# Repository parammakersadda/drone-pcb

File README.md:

# SNI drone (Stm32 + Nrf24l01+ + Imu drone)

(under early stage development)

open source drone printed circuit board design with 4 coreless motors,  
using [stm32f103c8](https://www.st.com/en/microcontrollers-microprocessors/stm32f103c8.html) microcontroller chip for processing data and motor control,  
and [nrf24l01+](https://www.nordicsemi.com/Products/nRF24-series) 2.4Ghz radio transciever chip for wireless communication.

# LICENSE

Licensed under CERN Open Hardware Licence Version 2 - Weakly Reciprocal  
check "LICENSE" file for the license

# Images

There are 3d model files available in the 3dModels folder, in both stl and glb file formats.

Pcb manufacturing files (gerbers) are exported into the **exports** folder

(schematic and the copper routing)'s PDF files are available in the **PDFs** folder

[3d model (stl)](3dModels/drone-pcb.stl)  

front  

back  

[Schematics (click on this link to see the PDF)](PDFs/drone-pcb.pdf)

[Pcb routing (click on this link to see the PDF)](PDFs/drone-pcb-B_Cu.pdf)

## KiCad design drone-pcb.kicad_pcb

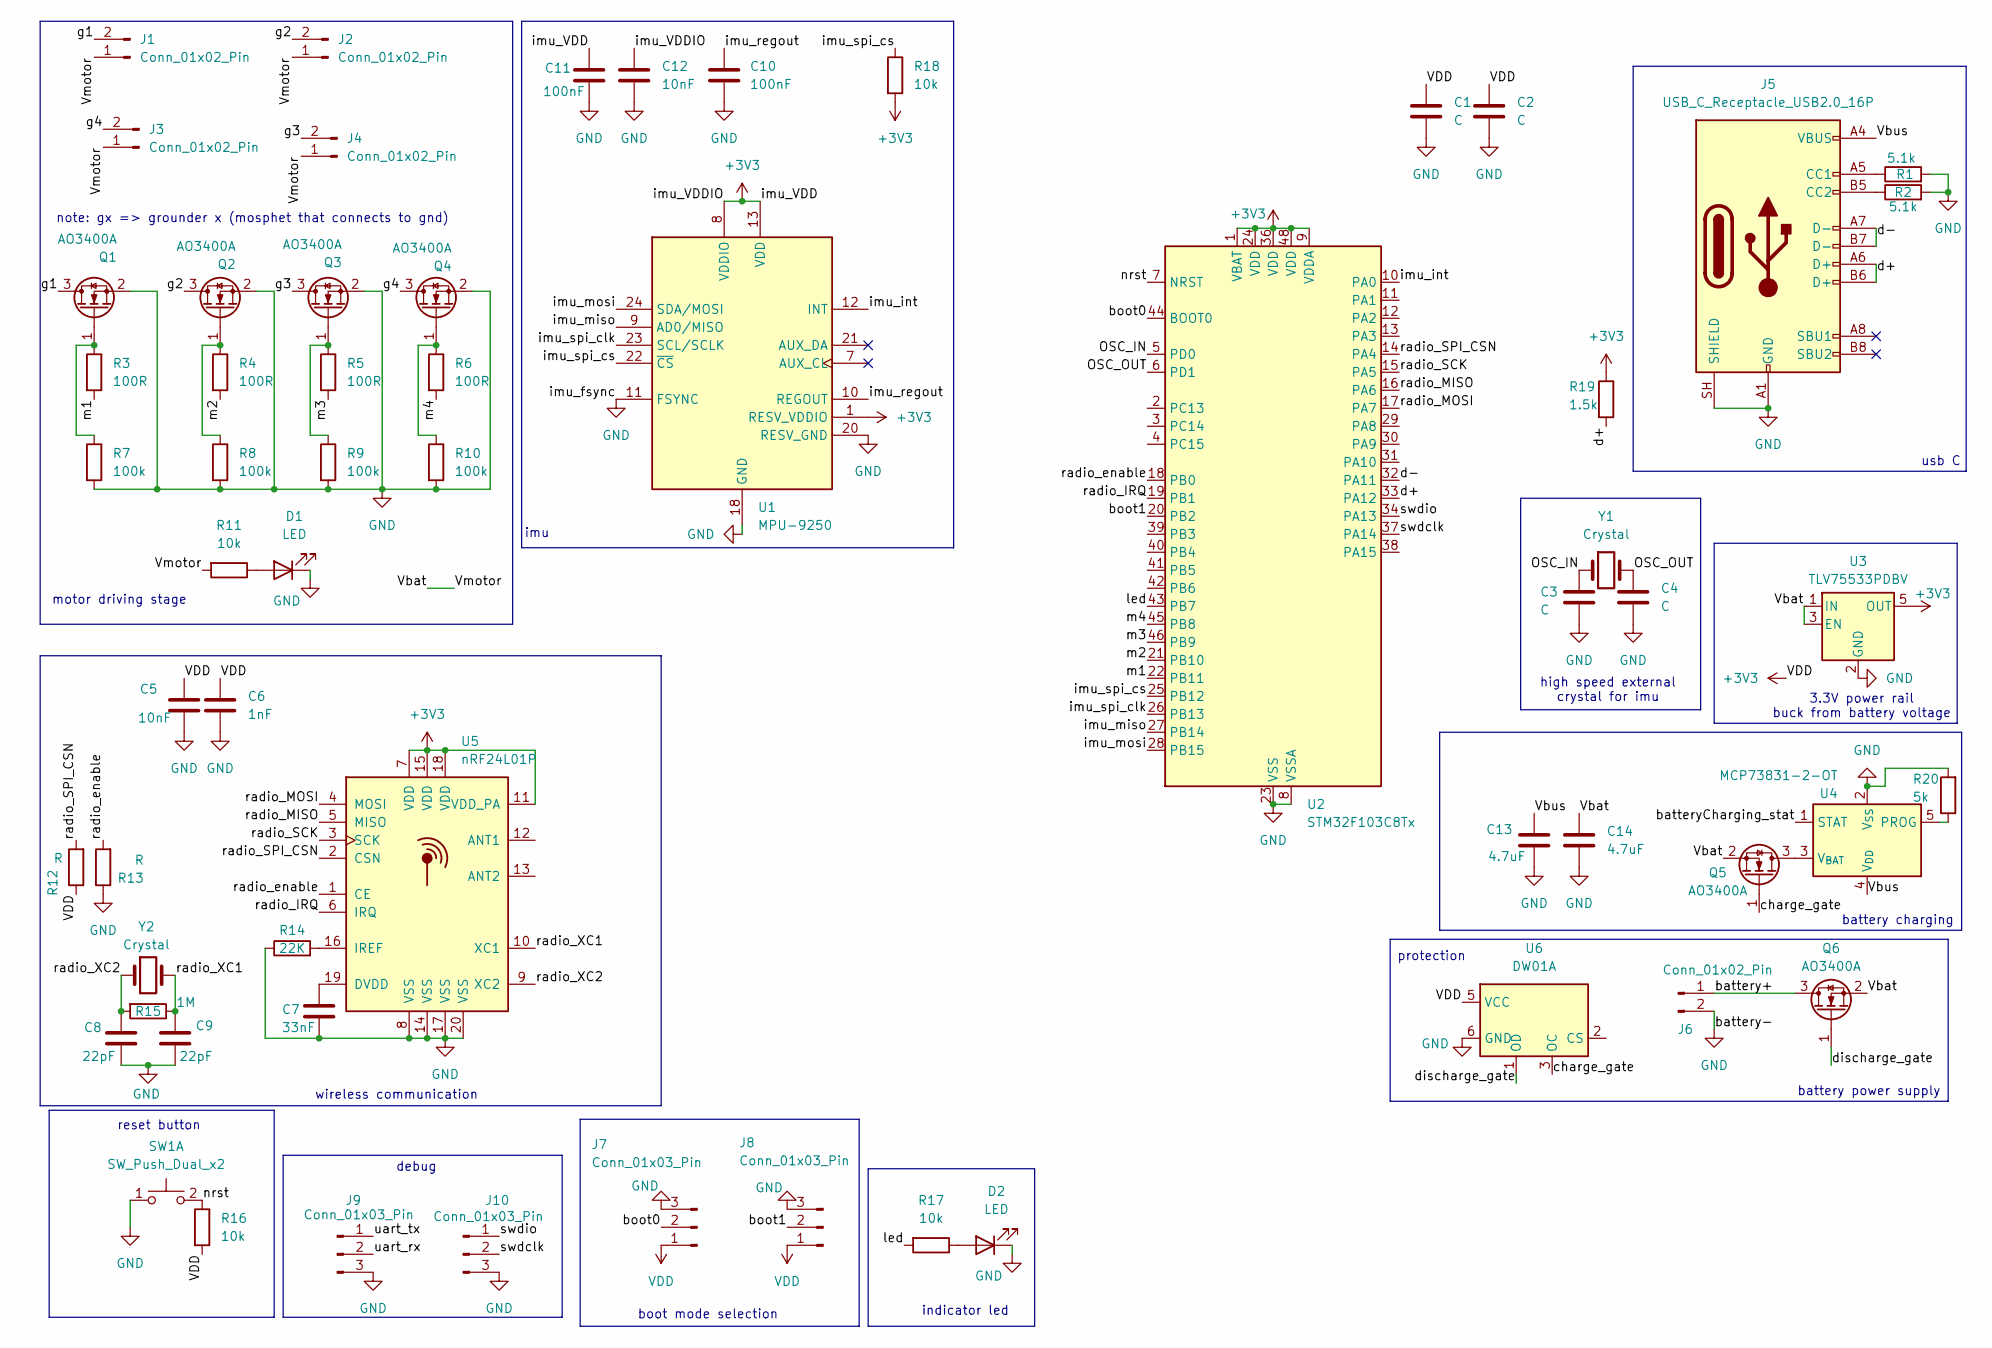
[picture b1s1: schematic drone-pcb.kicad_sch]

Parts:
C1, C2, C3, C4: C; C_0805_2012Metric_Pad1.18x1.45mm_HandSolder
C5, C12: 10nF; C_0805_2012Metric_Pad1.18x1.45mm_HandSolder
C6: 1nF; C_0805_2012Metric_Pad1.18x1.45mm_HandSolder
C7: 33nF; C_0805_2012Metric_Pad1.18x1.45mm_HandSolder
C8, C9: 22pF; C_0805_2012Metric_Pad1.18x1.45mm_HandSolder
C10, C11: 100nF; C_0805_2012Metric_Pad1.18x1.45mm_HandSolder
C13, C14: 4.7uF; C_0805_2012Metric_Pad1.18x1.45mm_HandSolder
D1, D2: LED; LED_0805_2012Metric_Pad1.15x1.40mm_HandSolder
J1, J2, J3, J4: Conn_01x02_Pin; JST_XH_S2B-XH-A-1_1x02_P2.50mm_Horizontal
J5: USB_C_Receptacle_USB2.0_16P; USB_C_Receptacle_HCTL_HC-TYPE-C-16P-01A
J6: Conn_01x02_Pin; JST_XH_B2B-XH-A_1x02_P2.50mm_Vertical
J7, J8, J9, J10: Conn_01x03_Pin; PinHeader_1x03_P2.54mm_Vertical
Q1, Q2, Q3, Q4, Q5, Q6: AO3400A; SOT-23
R1, R2: 5.1k; R_0603_1608Metric_Pad0.98x0.95mm_HandSolder
R3, R4, R5, R6: 100R; R_0603_1608Metric_Pad0.98x0.95mm_HandSolder
R7, R8, R9, R10: 100k; R_0603_1608Metric_Pad0.98x0.95mm_HandSolder
R11, R16, R17: 10k; R_0603_1608Metric_Pad0.98x0.95mm_HandSolder
R12, R13: R; R_0603_1608Metric_Pad0.98x0.95mm_HandSolder
R14: 22K; R_0603_1608Metric_Pad0.98x0.95mm_HandSolder
R15: 1M; R_0603_1608Metric_Pad0.98x0.95mm_HandSolder
R18: 10k
R19: 1.5k
R20: 5k
SW1: SW_Push_Dual_x2; smd-push-button-TS3425PA
U1: MPU-9250; InvenSense_QFN-24_3x3mm_P0.4mm
U2: STM32F103C8Tx; LQFP-48_7x7mm_P0.5mm
U3: TLV75533PDBV; SOT-23-5
U4: MCP73831-2-OT; SOT-23-5
U5: nRF24L01P; QFN-20-1EP_4x4mm_P0.5mm_EP2.5x2.5mm
U6: DW01A; SOT-23-6
Y1, Y2: Crystal

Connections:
+3V3: C1.1, C2.1, C5.1, C6.1, C11.1, C12.1, J7.1, J8.1, R12.1, R16.2, R18.2, R19.1, U1.1 (RESV_VDDIO), U1.8 (VDDIO), U1.13 (VDD), U2.1 (VBAT), U2.9 (VDDA), U2.24 (VDD), U2.36 (VDD), U2.48 (VDD), U3.5 (OUT), U5.7 (VDD), U5.11 (VDD_PA), U5.15 (VDD), U5.18 (VDD), U6.5 (VCC)
/OSC_IN: C3.1, U2.5 (PD0), Y1.1
/OSC_OUT: C4.1, U2.6 (PD1), Y1.2
/Vbat: C14.1, J1.1, J2.1, J3.1, J4.1, Q5.2 (S), Q6.2 (S), R11.2, U3.1 (IN), U3.3 (EN)
/Vbus: C13.1, J5.A4 (VBUS), J5.A9 (VBUS), J5.B4 (VBUS), J5.B9 (VBUS), U4.4 (V_{DD})
/battery+: J6.1, Q6.3 (D)
/batteryCharging_stat: U4.1 (STAT)
/boot0: J7.2, U2.44 (BOOT0)
/boot1: J8.2, U2.20 (PB2)
/charge_gate: Q5.1 (G), U6.3 (OC)
/d+: J5.A6 (D+), J5.B6 (D+), R19.2, U2.33 (PA12)
/d-: J5.A7 (D-), J5.B7 (D-), U2.32 (PA11)
/discharge_gate: Q6.1 (G), U6.1 (OD)
/g1: J1.2, Q1.3 (D)
/g2: J2.2, Q2.3 (D)
/g3: J4.2, Q3.3 (D)
/g4: J3.2, Q4.3 (D)
/imu_int: U1.12 (INT), U2.10 (PA0)
/imu_miso: U1.9 (AD0/MISO), U2.27 (PB14)
/imu_mosi: U1.24 (SDA/MOSI), U2.28 (PB15)
/imu_regout: C10.1, U1.10 (REGOUT)
/imu_spi_clk: U1.23 (SCL/SCLK), U2.26 (PB13)
/imu_spi_cs: R18.1, U1.22 (~CS), U2.25 (PB12)
/led: R17.2, U2.43 (PB7)
/m1: R3.2, U2.22 (PB11)
/m2: R4.2, U2.21 (PB10)
/m3: R5.2, U2.46 (PB9)
/m4: R6.2, U2.45 (PB8)
/nrst: R16.1, SW1.2 (D), U2.7 (NRST)
/radio_IRQ: U2.19 (PB1), U5.6 (IRQ)
/radio_MISO: U2.16 (PA6), U5.5 (MISO)
/radio_MOSI: U2.17 (PA7), U5.4 (MOSI)
/radio_SCK: U2.15 (PA5), U5.3 (SCK)
/radio_SPI_CSN: R12.2, U2.14 (PA4), U5.2 (CSN)
/radio_XC1: C9.1, R15.1, U5.10 (XC1), Y2.2
/radio_XC2: C8.1, R15.2, U5.9 (XC2), Y2.1
/radio_enable: R13.2, U2.18 (PB0), U5.1 (CE)
/swdclk: J10.2, U2.37 (PA14)
/swdio: J10.1, U2.34 (PA13)
/uart_rx: J9.2
/uart_tx: J9.1
GND: C1.2, C2.2, C3.2, C4.2, C5.2, C6.2, C7.2, C8.2, C9.2, C10.2, C11.2, C12.2, C13.2, C14.2, D1.1 (K), D2.1 (K), J5.A1 (GND), J5.A12 (GND), J5.B1 (GND), J5.B12 (GND), J5.SH (SHIELD), J6.2, J7.3, J8.3, J9.3, J10.3, Q1.2 (S), Q2.2 (S), Q3.2 (S), Q4.2 (S), R1.2, R2.2, R7.2, R8.2, R9.2, R10.2, R13.1, R14.1, R20.2, SW1.1 (C), U1.11 (FSYNC), U1.18 (GND), U1.20 (RESV_GND), U2.8 (VSSA), U2.23 (VSS), U2.35 (VSS), U2.47 (VSS), U3.2 (GND), U4.2 (V_{SS}), U5.8 (VSS), U5.14 (VSS), U5.17 (VSS), U5.20 (VSS), U6.6 (GND)
unnamed: D1.2 (A), R11.1
unnamed: D2.2 (A), R17.1
unnamed: J5.A5 (CC1), R1.1
unnamed: J5.B5 (CC2), R2.1
unnamed: Q1.1 (G), R3.1, R7.1
unnamed: Q2.1 (G), R4.1, R8.1
unnamed: Q3.1 (G), R5.1, R9.1
unnamed: Q4.1 (G), R6.1, R10.1
unnamed: Q5.3 (D), U4.3 (V_{BAT})
unnamed: R20.1, U4.5 (PROG)
unnamed: C7.1, U5.19 (DVDD)
unnamed: R14.2, U5.16 (IREF)

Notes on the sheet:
imu
battery power supply
usb C
debug
note: gx => grounder x (mosphet that connects to gnd)
motor driving stage
3.3V power rail buck from battery voltage
high speed external crystal for imu
battery charging
indicator led
boot mode selection
protection
wireless communication
reset button

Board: 2 copper layers, 56 parts (34 on the bottom side), 50 nets, no tracks yet.

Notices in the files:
drone-pcb.kicad_pcb:
licensed under: CERN-OHL-W V2.0
license: CERN-OHL-W V2.0
